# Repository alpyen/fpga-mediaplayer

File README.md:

# fpga-mediaplayer - learning FPGA development

Hi there, and welcome to my FPGA project to deep dive into FPGA development and everything around it.

Watch a demo of this project on YouTube by clicking on this picture!

## Navigation
1. [Introduction](#introduction)
2. [Project Goal](#project-goal)
3. [Top Level Overview](#top-level-overview)
4. [Documentation](#documentation)

## Introduction

This is a beginner project on hardware development with FPGAs and VHDL to create a system that can
play audio and video through an FPGA.

A FPGA development board -- here a <a href="https://digilent.com/reference/programmable-logic/basys-3/start">Digilent Basys3</a>
-- fetches audio and video data stored on the on-board flash memory chip,
decodes them and drives a <a href="https://digilent.com/reference/pmod/pmodi2s2/start">Digilent i2s2-PMOD</a>
for audio output and a custom designedLED matrix as the video display.

Originally the idea was to drive one of these standard Arduino LED shields (14x9 pixels) but that plan
was scrapped due to the very low resolution.

The key focus of this project was to accomplish this vision with certain -- partially arbitrary -- constraints
and to get the whole thing done while touching on many aspects of FPGA and electronics development.
It is by no means perfect, but it is done while hitting all the project's goals I set for myself.

## Project Goal

The main goal of this project was to get my hands dirty with all parts of FPGA development.
While the main focus is on the actual hardware description, a good amount of time was also spent
on developing the software and electronics side of things to get the full picture.

Besides getting this project actually done,
there were a lot of topics I wanted to cover (which includes, but is not limited to):
- Develop a full FPGA project with everything necessary
- Keep it flexible that it could run on different devices without too much additional effort
- Write HDL and verify with testbenches
- Write packages and make them accessible
- Make use of existing IP
- Prototyping
- Schematics, Layouting and Manufacturing a PCB
- Interface with other onboard components such as the flash memory
- Interface with prebuilt offboard components such as the Digilent I2S2 PMOD
- Interface with external offboard components such as the LED board
- Work within the limits of the given board such as the Digilent Basys3 (Artix7-35T)
  - 4MB Flash (only ~2MB with configuration)
  - Available IO
  - Clock Speed to maintain realtime
- Software development
  - Codec for audio and video
- Miscellaneous
  - Organization of project structure and repository for Git
  - Documentation of the whole project

Please note that these constraints emerged from the components and devices I have at disposal.
This project could be done with greater resolution and sound output but the goal is to bring it up
and learn everything along the way, that's the reason behind this approach.

## Top Level Overview

Here's a top level view of the system. It is build in a modular fashion encapsulating functionality
such that everything remains as local as possible so each module is easy to understand.
Dataflow is indicated by the directional arrows.

The Control Unit requests data from the memory driver which (here) accesses the onboard SPI flash.
It then alternately fills the Audio and Video FIFO which are read by the respective modules
on the other side. Those decode the data and fill up a FIFO for Audio and BRAMs for Video.
After the data is available the i2s Master and Board Driver will read the data at the correct time and
play them back by driving a Digilent i2s2 PMOD and a self designed LED multiplex display.

<picture>
    <source media="(prefers-color-scheme: dark)" srcset="docs/images/top-level-view-dark.png">
    
</picture>

## Documentation

A technical overview as well as project notes and decision making
can be found in the documentation.
Find the documentation overview [here](docs/README.md).

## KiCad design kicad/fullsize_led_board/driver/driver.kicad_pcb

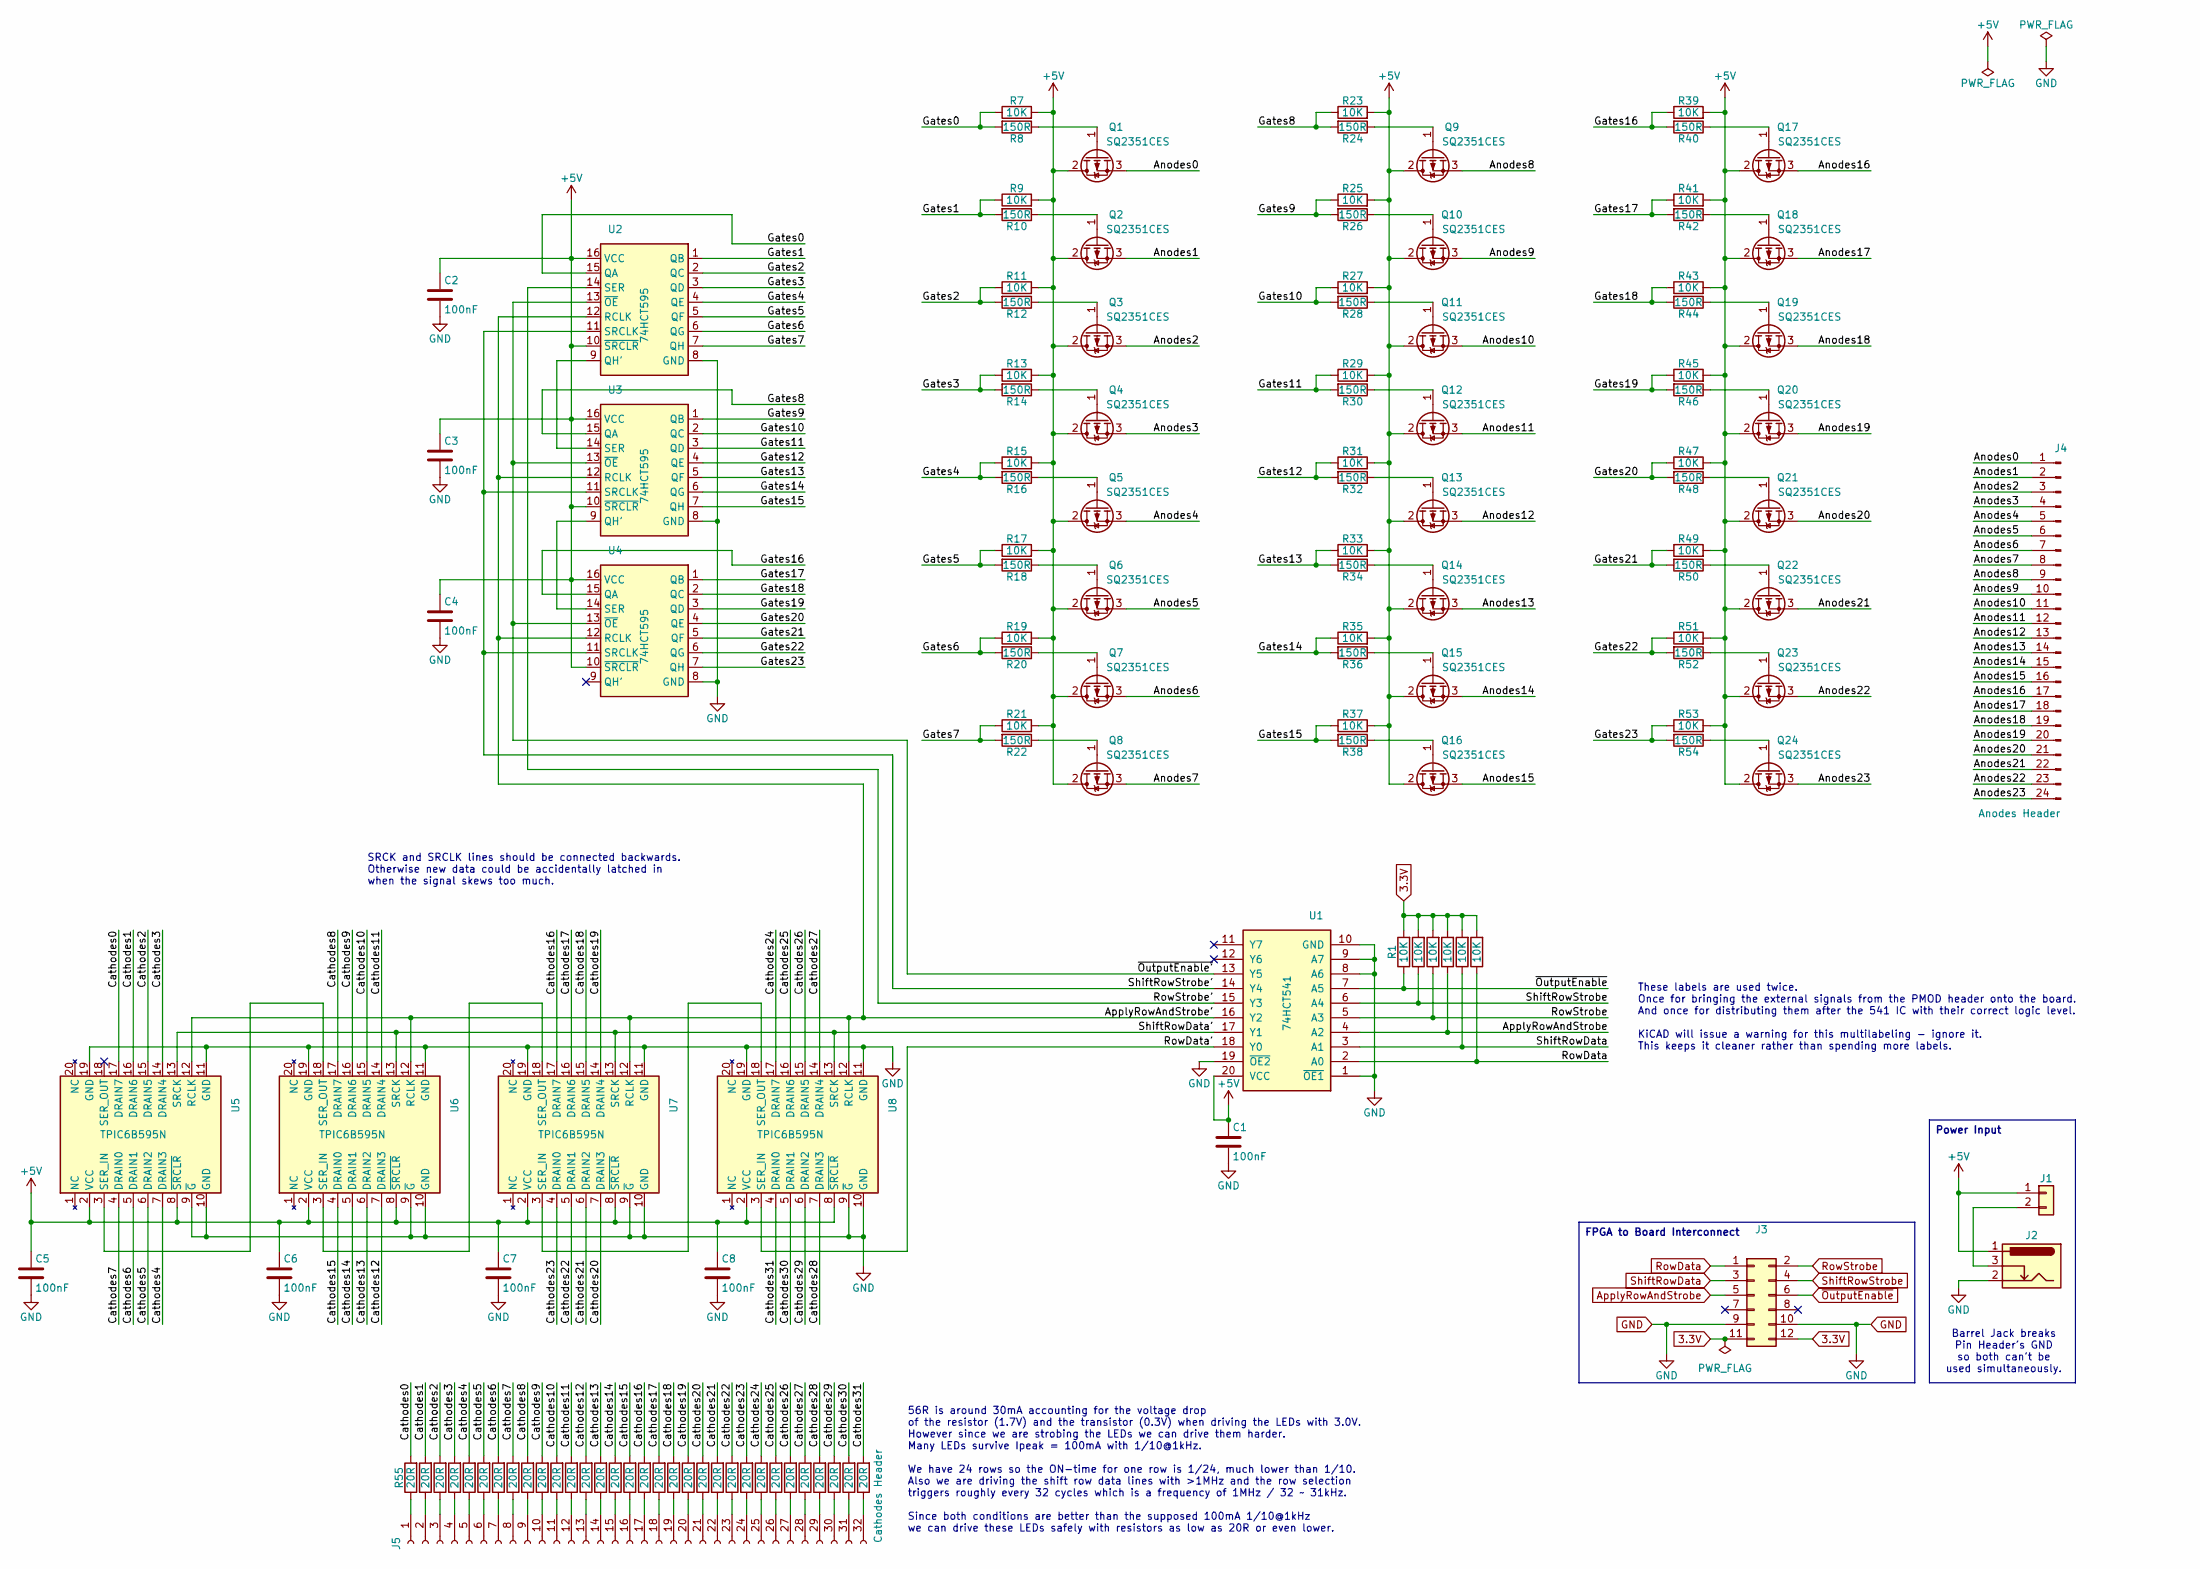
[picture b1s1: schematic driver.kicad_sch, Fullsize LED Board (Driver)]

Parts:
C1, C2, C3, C4, C5, C6, C7, C8: 100nF; C_Disc_D4.7mm_W2.5mm_P5.00mm
J1: PinHeader_1x02_P2.54mm_Horizontal
J2: BarrelJack_Horizontal
J3: PinHeader_2x06_P2.54mm_Horizontal
J4: Anodes Header; PinSocket_1x24_P2.54mm_Vertical
J5: Cathodes Header; PinSocket_1x32_P2.54mm_Vertical
Q1, Q2, Q3, Q4, Q5, Q6, Q7, Q8, Q9, Q10, Q11, Q12, Q13, Q14, Q15, Q16, Q17, Q18, Q19, Q20, Q21, Q22, Q23, Q24: SQ2351CES; SOT-23-3
R1, R2, R3, R4, R5, R6, R7, R9, R11, R13, R15, R17, R19, R21, R23, R25, R27, R29, R31, R33, R35, R37, R39, R41, R43, R45, R47, R49, R51, R53: 10K; R_Axial_DIN0207_L6.3mm_D2.5mm_P7.62mm_Horizontal
R8, R10, R12, R14, R16, R18, R20, R22, R24, R26, R28, R30, R32, R34, R36, R38, R40, R42, R44, R46, R48, R50, R52, R54: 150R; R_Axial_DIN0207_L6.3mm_D2.5mm_P7.62mm_Horizontal
R55, R56, R57, R58, R59, R60, R61, R62, R63, R64, R65, R66, R67, R68, R69, R70, R71, R72, R73, R74, R75, R76, R77, R78, R79, R80, R81, R82, R83, R84, R85, R86: 20R; R_Axial_DIN0207_L6.3mm_D2.5mm_P7.62mm_Horizontal
U1: 74HCT541; DIP-20_W7.62mm
U2, U3, U4: 74HCT595; SOIC-16_3.9x9.9mm_P1.27mm
U5, U6, U7, U8: TPIC6B595N; DIP-20_W7.62mm

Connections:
3.3V: J3.11, J3.12, R1.2, R2.2, R3.2, R4.2, R5.2, R6.2
+5V: C1.1, C2.1, C3.1, C4.1, C5.1, C6.1, C7.1, C8.1, J1.1, J2.1, Q1.2 (S), Q2.2 (S), Q3.2 (S), Q4.2 (S), Q5.2 (S), Q6.2 (S), Q7.2 (S), Q8.2 (S), Q9.2 (S), Q10.2 (S), Q11.2 (S), Q12.2 (S), Q13.2 (S), Q14.2 (S), Q15.2 (S), Q16.2 (S), Q17.2 (S), Q18.2 (S), Q19.2 (S), Q20.2 (S), Q21.2 (S), Q22.2 (S), Q23.2 (S), Q24.2 (S), R7.2, R9.2, R11.2, R13.2, R15.2, R17.2, R19.2, R21.2, R23.2, R25.2, R27.2, R29.2, R31.2, R33.2, R35.2, R37.2, R39.2, R41.2, R43.2, R45.2, R47.2, R49.2, R51.2, R53.2, U1.20 (VCC), U2.10 (~SRCLR), U2.16 (VCC), U3.10 (~SRCLR), U3.16 (VCC), U4.10 (~SRCLR), U4.16 (VCC), U5.2 (VCC), U5.8 (~SRCLR), U6.2 (VCC), U6.8 (~SRCLR), U7.2 (VCC), U7.8 (~SRCLR), U8.2 (VCC), U8.8 (~SRCLR)
/Anodes0: J4.1, Q1.3 (D)
/Anodes1: J4.2, Q2.3 (D)
/Anodes2: J4.3, Q3.3 (D)
/Anodes3: J4.4, Q4.3 (D)
/Anodes4: J4.5, Q5.3 (D)
/Anodes5: J4.6, Q6.3 (D)
/Anodes6: J4.7, Q7.3 (D)
/Anodes7: J4.8, Q8.3 (D)
/Anodes8: J4.9, Q9.3 (D)
/Anodes9: J4.10, Q10.3 (D)
/Anodes10: J4.11, Q11.3 (D)
/Anodes11: J4.12, Q12.3 (D)
/Anodes12: J4.13, Q13.3 (D)
/Anodes13: J4.14, Q14.3 (D)
/Anodes14: J4.15, Q15.3 (D)
/Anodes15: J4.16, Q16.3 (D)
/Anodes16: J4.17, Q17.3 (D)
/Anodes17: J4.18, Q18.3 (D)
/Anodes18: J4.19, Q19.3 (D)
/Anodes19: J4.20, Q20.3 (D)
/Anodes20: J4.21, Q21.3 (D)
/Anodes21: J4.22, Q22.3 (D)
/Anodes22: J4.23, Q23.3 (D)
/Anodes23: J4.24, Q24.3 (D)
/ApplyRowAndStrobe': U1.16 (Y2), U2.12 (RCLK), U3.12 (RCLK), U4.12 (RCLK), U5.12 (RCLK), U6.12 (RCLK), U7.12 (RCLK), U8.12 (RCLK)
/Cathodes0: R55.2, U5.17 (DRAIN7)
/Cathodes1: R56.2, U5.16 (DRAIN6)
/Cathodes2: R57.2, U5.15 (DRAIN5)
/Cathodes3: R58.2, U5.14 (DRAIN4)
/Cathodes4: R59.2, U5.7 (DRAIN3)
/Cathodes5: R60.2, U5.6 (DRAIN2)
/Cathodes6: R61.2, U5.5 (DRAIN1)
/Cathodes7: R62.2, U5.4 (DRAIN0)
/Cathodes8: R63.2, U6.17 (DRAIN7)
/Cathodes9: R64.2, U6.16 (DRAIN6)
/Cathodes10: R65.2, U6.15 (DRAIN5)
/Cathodes11: R66.2, U6.14 (DRAIN4)
/Cathodes12: R67.2, U6.7 (DRAIN3)
/Cathodes13: R68.2, U6.6 (DRAIN2)
/Cathodes14: R69.2, U6.5 (DRAIN1)
/Cathodes15: R70.2, U6.4 (DRAIN0)
/Cathodes16: R71.2, U7.17 (DRAIN7)
/Cathodes17: R72.2, U7.16 (DRAIN6)
/Cathodes18: R73.2, U7.15 (DRAIN5)
/Cathodes19: R74.2, U7.14 (DRAIN4)
/Cathodes20: R75.2, U7.7 (DRAIN3)
/Cathodes21: R76.2, U7.6 (DRAIN2)
/Cathodes22: R77.2, U7.5 (DRAIN1)
/Cathodes23: R78.2, U7.4 (DRAIN0)
/Cathodes24: R79.2, U8.17 (DRAIN7)
/Cathodes25: R80.2, U8.16 (DRAIN6)
/Cathodes26: R81.2, U8.15 (DRAIN5)
/Cathodes27: R82.2, U8.14 (DRAIN4)
/Cathodes28: R83.2, U8.7 (DRAIN3)
/Cathodes29: R84.2, U8.6 (DRAIN2)
/Cathodes30: R85.2, U8.5 (DRAIN1)
/Cathodes31: R86.2, U8.4 (DRAIN0)
/Gates0: R7.1, R8.2, U2.15 (QA)
/Gates1: R9.1, R10.2, U2.1 (QB)
/Gates2: R11.1, R12.2, U2.2 (QC)
/Gates3: R13.1, R14.2, U2.3 (QD)
/Gates4: R15.1, R16.2, U2.4 (QE)
/Gates5: R17.1, R18.2, U2.5 (QF)
/Gates6: R19.1, R20.2, U2.6 (QG)
/Gates7: R21.1, R22.2, U2.7 (QH)
/Gates8: R23.1, R24.2, U3.15 (QA)
/Gates9: R25.1, R26.2, U3.1 (QB)
/Gates10: R27.1, R28.2, U3.2 (QC)
/Gates11: R29.1, R30.2, U3.3 (QD)
/Gates12: R31.1, R32.2, U3.4 (QE)
/Gates13: R33.1, R34.2, U3.5 (QF)
/Gates14: R35.1, R36.2, U3.6 (QG)
/Gates15: R37.1, R38.2, U3.7 (QH)
/Gates16: R39.1, R40.2, U4.15 (QA)
/Gates17: R41.1, R42.2, U4.1 (QB)
/Gates18: R43.1, R44.2, U4.2 (QC)
/Gates19: R45.1, R46.2, U4.3 (QD)
/Gates20: R47.1, R48.2, U4.4 (QE)
/Gates21: R49.1, R50.2, U4.5 (QF)
/Gates22: R51.1, R52.2, U4.6 (QG)
/Gates23: R53.1, R54.2, U4.7 (QH)
/RowData': U1.18 (Y0), U8.3 (SER_IN)
/RowStrobe': U1.15 (Y3), U2.14 (SER)
/ShiftRowData': U1.17 (Y1), U5.13 (SRCK), U6.13 (SRCK), U7.13 (SRCK), U8.13 (SRCK)
/ShiftRowStrobe': U1.14 (Y4), U2.11 (SRCLK), U3.11 (SRCLK), U4.11 (SRCLK)
/~OutputEnable': U1.13 (Y5), U2.13 (~OE), U3.13 (~OE), U4.13 (~OE)
ApplyRowAndStrobe: J3.5, R4.1, U1.4 (A2)
GND: C1.2, C2.2, C3.2, C4.2, C5.2, C6.2, C7.2, C8.2, J2.2, J3.9, J3.10, U1.1 (~OE1), U1.8 (A6), U1.9 (A7), U1.10 (GND), U1.19 (~OE2), U2.8 (GND), U3.8 (GND), U4.8 (GND), U5.9 (~G), U5.10 (GND), U5.11 (GND), U5.19 (GND), U6.9 (~G), U6.10 (GND), U6.11 (GND), U6.19 (GND), U7.9 (~G), U7.10 (GND), U7.11 (GND), U7.19 (GND), U8.9 (~G), U8.10 (GND), U8.11 (GND), U8.19 (GND)
unnamed: J1.2, J2.3
unnamed: J5.1, R55.1
unnamed: J5.2, R56.1
unnamed: J5.3, R57.1
unnamed: J5.4, R58.1
unnamed: J5.5, R59.1
unnamed: J5.6, R60.1
unnamed: J5.7, R61.1
unnamed: J5.8, R62.1
unnamed: J5.9, R63.1
unnamed: J5.10, R64.1
unnamed: J5.11, R65.1
unnamed: J5.12, R66.1
unnamed: J5.13, R67.1
unnamed: J5.14, R68.1
unnamed: J5.15, R69.1
unnamed: J5.16, R70.1
unnamed: J5.17, R71.1
unnamed: J5.18, R72.1
unnamed: J5.19, R73.1
unnamed: J5.20, R74.1
unnamed: J5.21, R75.1
unnamed: J5.22, R76.1
unnamed: J5.23, R77.1
unnamed: J5.24, R78.1
unnamed: J5.25, R79.1
unnamed: J5.26, R80.1
unnamed: J5.27, R81.1
unnamed: J5.28, R82.1
unnamed: J5.29, R83.1
unnamed: J5.30, R84.1
unnamed: J5.31, R85.1
unnamed: J5.32, R86.1
unnamed: Q1.1 (G), R8.1
unnamed: Q2.1 (G), R10.1
unnamed: Q3.1 (G), R12.1
unnamed: Q4.1 (G), R14.1
unnamed: Q5.1 (G), R16.1
unnamed: Q6.1 (G), R18.1
unnamed: Q7.1 (G), R20.1
unnamed: Q8.1 (G), R22.1
unnamed: Q9.1 (G), R24.1
unnamed: Q10.1 (G), R26.1
unnamed: Q11.1 (G), R28.1
unnamed: Q12.1 (G), R30.1
unnamed: Q13.1 (G), R32.1
unnamed: Q14.1 (G), R34.1
unnamed: Q15.1 (G), R36.1
unnamed: Q16.1 (G), R38.1
unnamed: Q17.1 (G), R40.1
unnamed: Q18.1 (G), R42.1
unnamed: Q19.1 (G), R44.1
unnamed: Q20.1 (G), R46.1
unnamed: Q21.1 (G), R48.1
unnamed: Q22.1 (G), R50.1
unnamed: Q23.1 (G), R52.1
unnamed: Q24.1 (G), R54.1
unnamed: U2.9 (QH'), U3.14 (SER)
unnamed: U3.9 (QH'), U4.14 (SER)
unnamed: U5.3 (SER_IN), U6.18 (SER_OUT)
unnamed: U6.3 (SER_IN), U7.18 (SER_OUT)
unnamed: U7.3 (SER_IN), U8.18 (SER_OUT)
RowData: J3.1, R6.1, U1.2 (A0)
RowStrobe: J3.2, R3.1, U1.5 (A3)
ShiftRowData: J3.3, R5.1, U1.3 (A1)
ShiftRowStrobe: J3.4, R2.1, U1.6 (A4)
~OutputEnable: J3.6, R1.1, U1.7 (A5)

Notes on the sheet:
56R is around 30mA accounting for the voltage drop of the resistor (1.7V) and the transistor (0.3V) when driving the LEDs with 3.0V. However since we are strobing the LEDs we can drive them harder. Many LEDs survive Ipeak = 100mA with 1/10@1kHz. We have 24 rows so the ON-time for one row is 1/24, m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
Barrel Jack breaks Pin Header's GND so both can't be used simultaneously.
These labels are used twice. Once for bringing the external signals from the PMOD header onto the board. And once for distributing them after the 541 IC with their correct logic level. KiCAD will issue a warning for this multilabeling - ignore it. This keeps it cleaner rather than spending more lab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
SRCK and SRCLK lines should be connected backwards. Otherwise new data could be accidentally latched in when the signal skews too much.
Power Input
FPGA to Board Interconnect

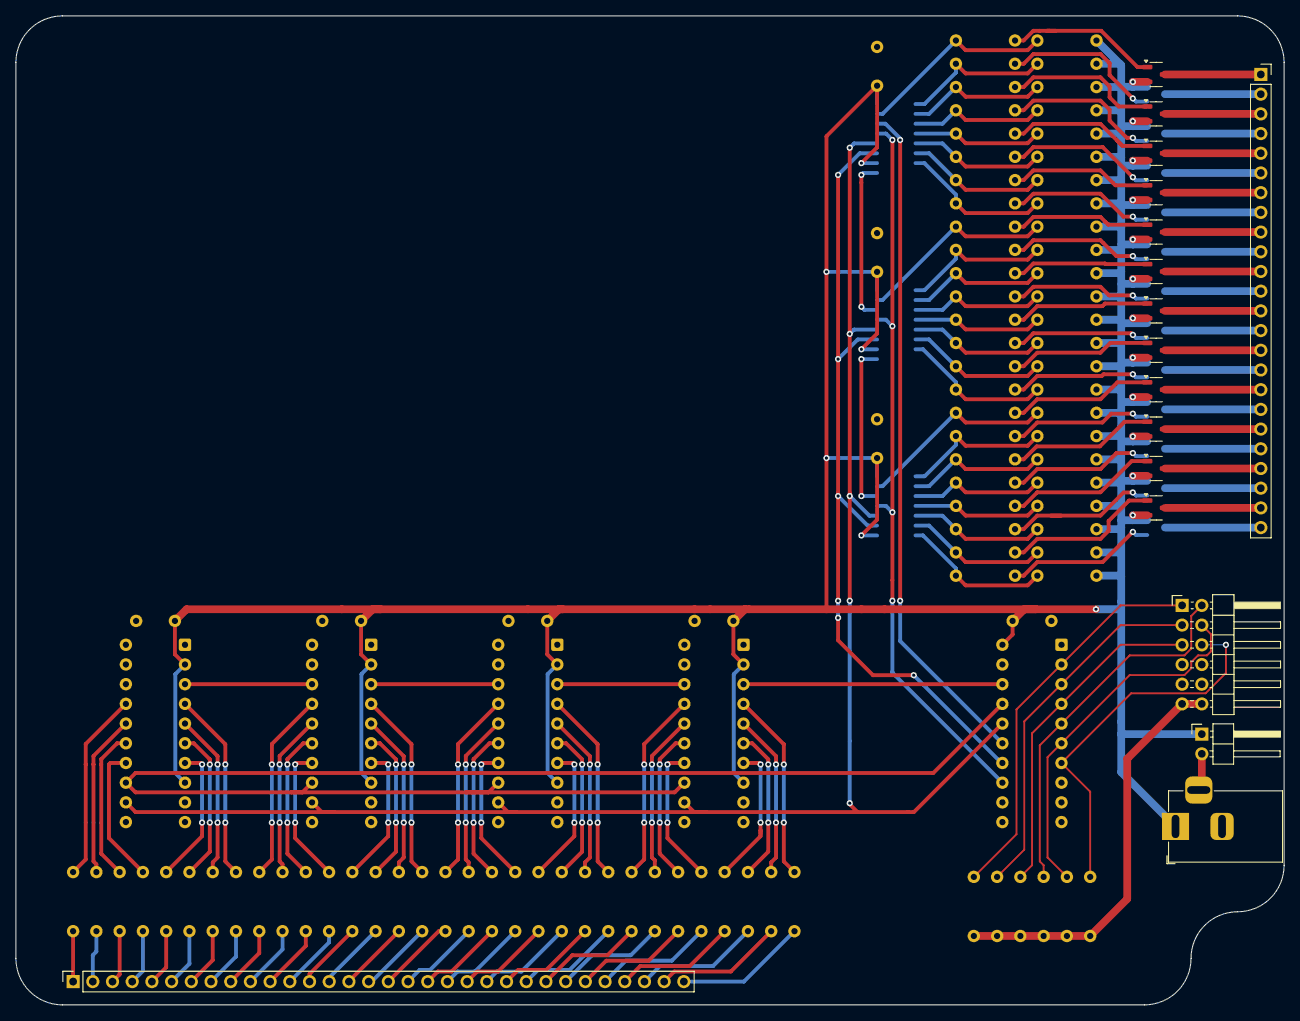
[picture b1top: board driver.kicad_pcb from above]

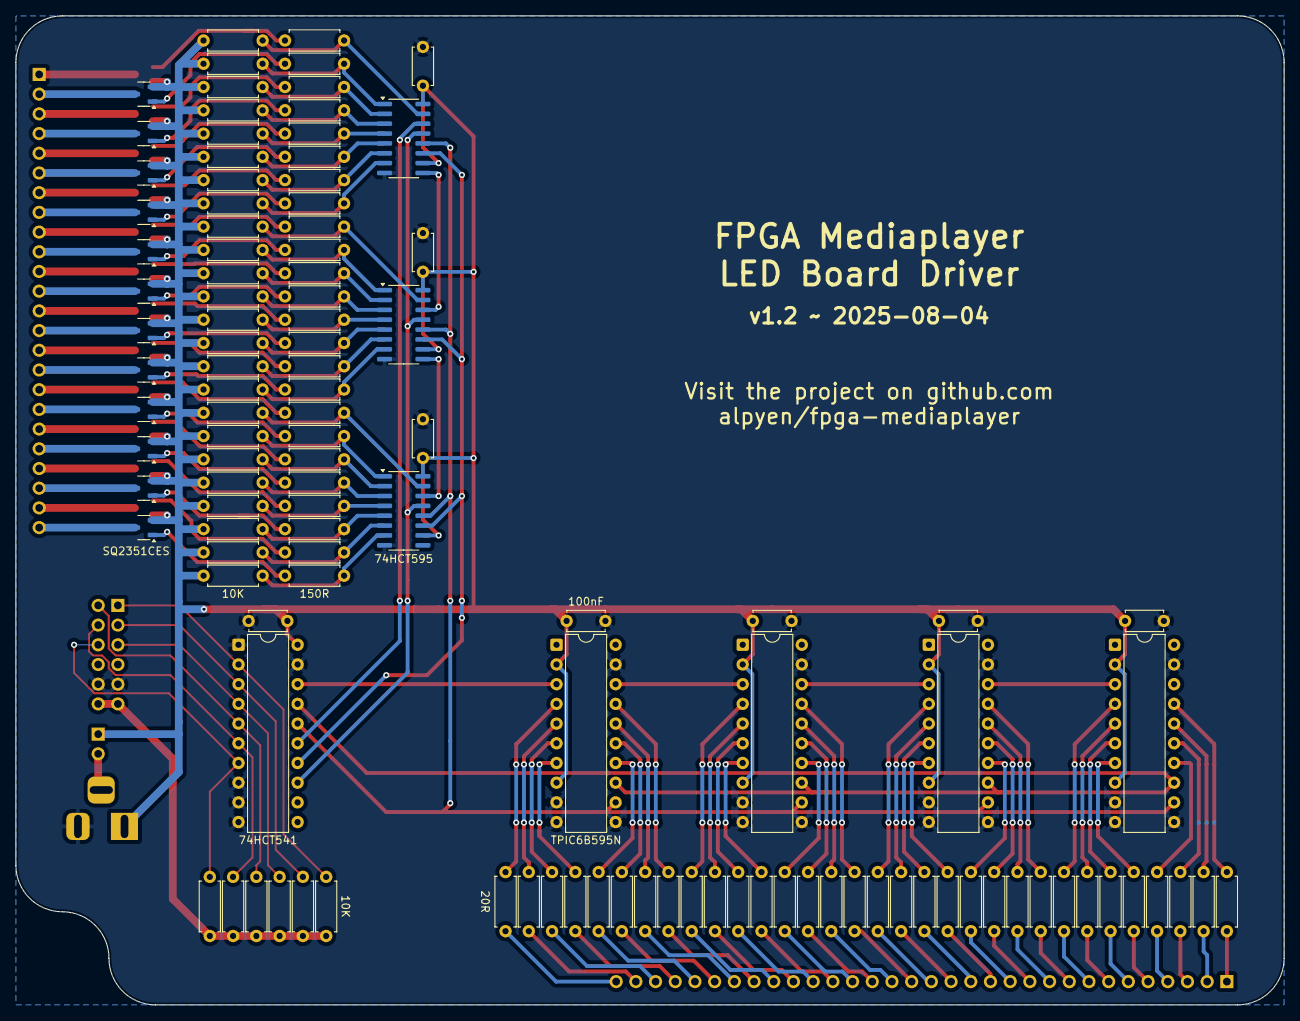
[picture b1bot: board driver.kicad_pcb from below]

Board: 2 copper layers, 163.5 x 127.5 mm, 131 parts (114 on the bottom side), 157 nets.

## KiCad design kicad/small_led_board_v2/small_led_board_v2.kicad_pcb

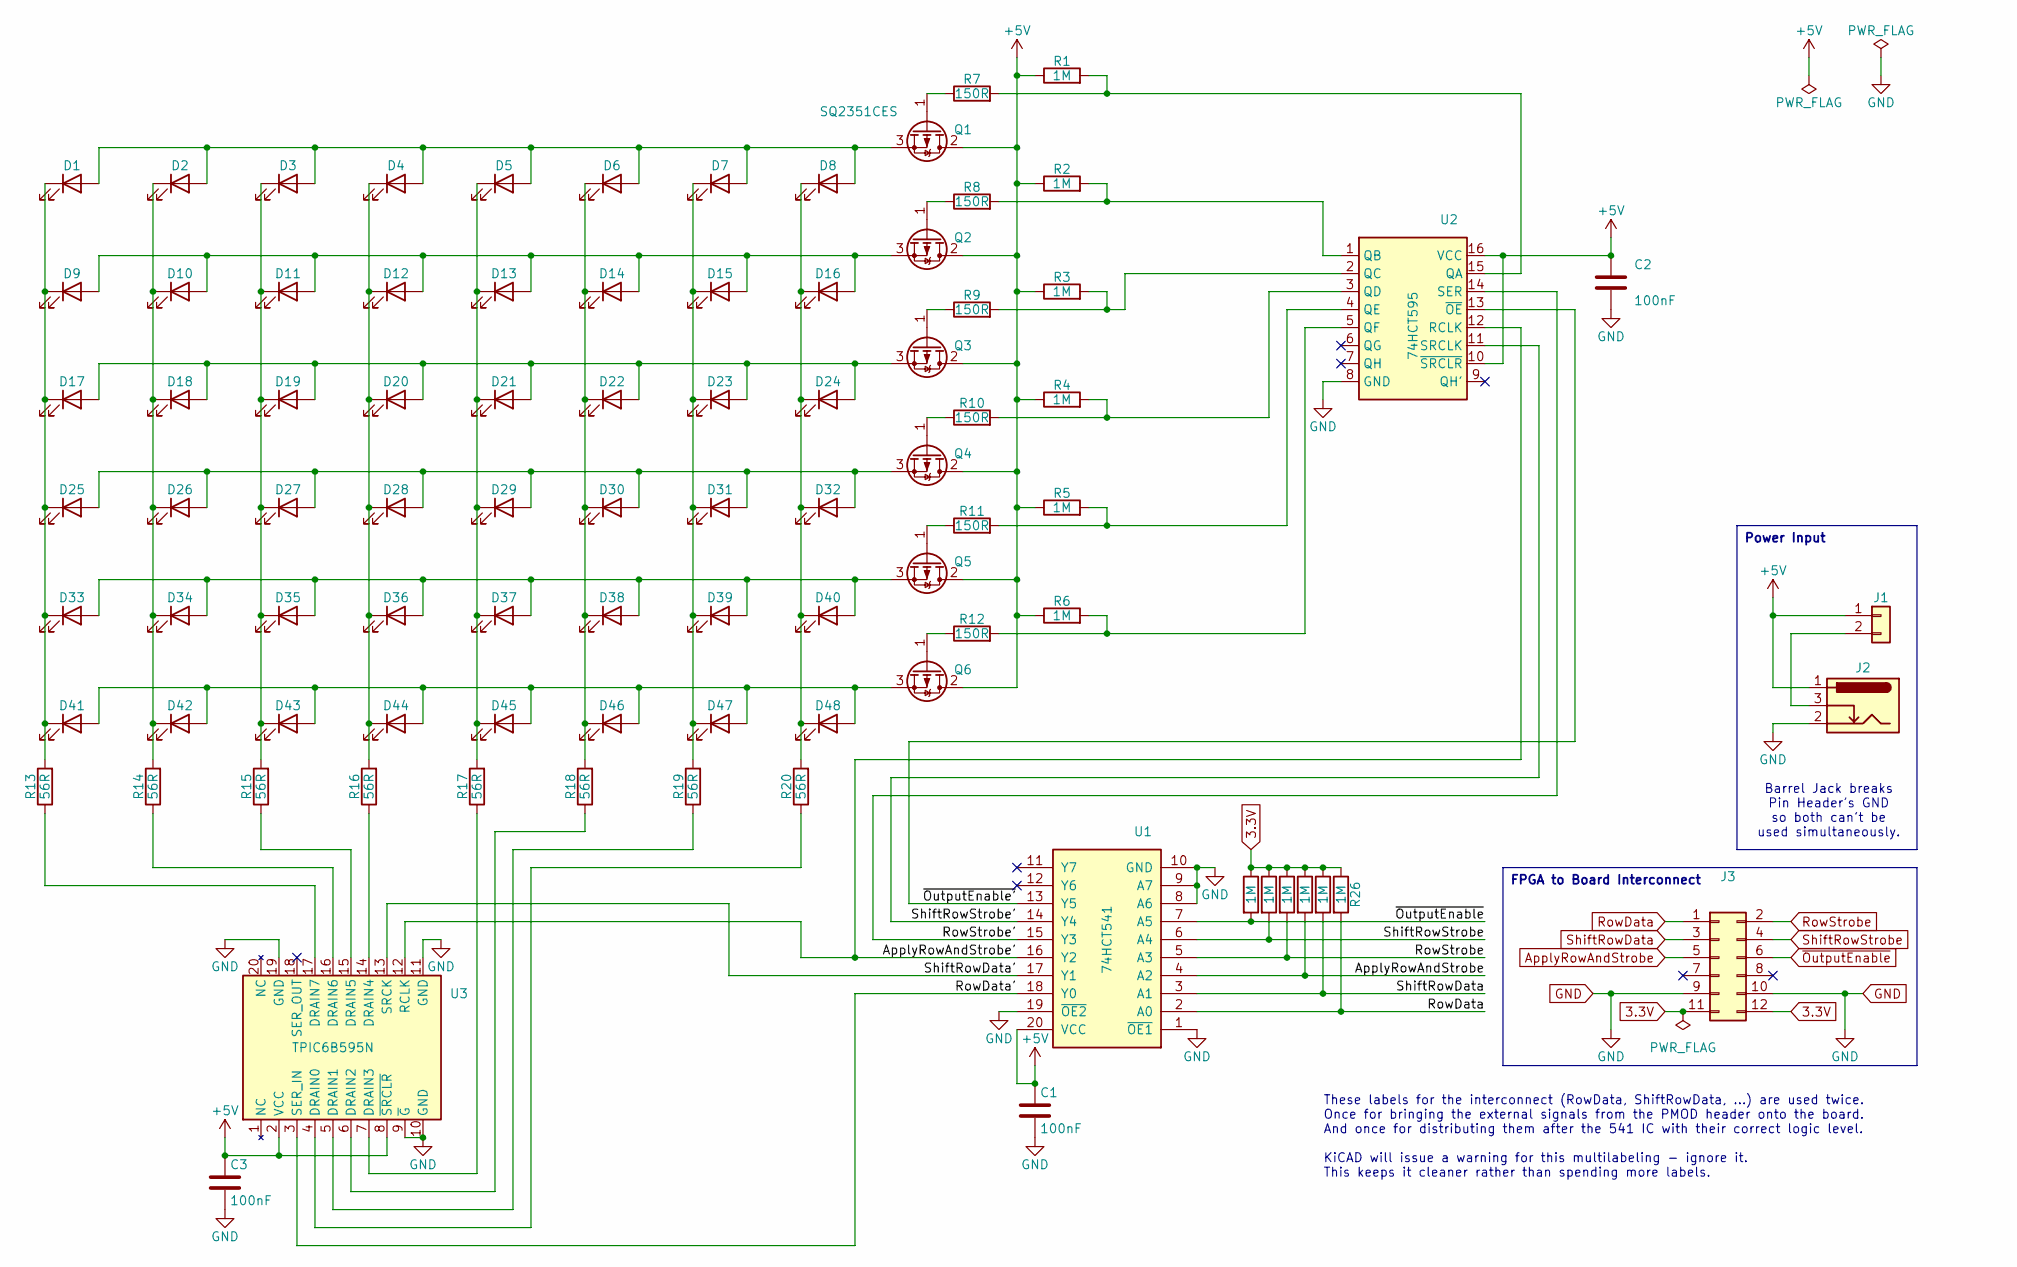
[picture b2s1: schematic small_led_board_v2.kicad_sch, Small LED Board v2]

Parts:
C1, C2, C3: 100nF; C_Disc_D4.7mm_W2.5mm_P5.00mm
D1, D2, D3, D4, D5, D6, D7, D8, D9, D10, D11, D12, D13, D14, D15, D16, D17, D18, D19, D20, D21, D22, D23, D24, D25, D26, D27, D28, D29, D30, D31, D32, D33, D34, D35, D36, D37, D38, D39, D40, D41, D42, D43, D44, D45, D46, D47, D48: LED; LED_D5.0mm
J1: PinHeader_1x02_P2.54mm_Horizontal
J2: BarrelJack_Horizontal
J3: PinHeader_2x06_P2.54mm_Horizontal
Q1, Q2, Q3, Q4, Q5, Q6: SQ2351CES; SOT-23-3
R1, R2, R3, R4, R5, R6, R21, R22, R23, R24, R25, R26: 1M; R_Axial_DIN0207_L6.3mm_D2.5mm_P7.62mm_Horizontal
R7, R8, R9, R10, R11, R12: 150R; R_Axial_DIN0207_L6.3mm_D2.5mm_P7.62mm_Horizontal
R13, R14, R15, R16, R17, R18, R19, R20: 56R; R_Axial_DIN0207_L6.3mm_D2.5mm_P7.62mm_Horizontal
U1: 74HCT541; DIP-20_W7.62mm
U2: 74HCT595; SOIC-16_3.9x9.9mm_P1.27mm
U3: TPIC6B595N; DIP-20_W7.62mm

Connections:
3.3V: J3.11, J3.12, R21.1, R22.1, R23.1, R24.1, R25.1, R26.1
+5V: C1.1, C2.1, C3.1, J1.1, J2.1, Q1.2 (S), Q2.2 (S), Q3.2 (S), Q4.2 (S), Q5.2 (S), Q6.2 (S), R1.1, R2.1, R3.1, R4.1, R5.1, R6.1, U1.20 (VCC), U2.10 (~SRCLR), U2.16 (VCC), U3.2 (VCC), U3.8 (~SRCLR)
/ApplyRowAndStrobe': U1.16 (Y2), U2.12 (RCLK), U3.12 (RCLK)
/RowData': U1.18 (Y0), U3.3 (SER_IN)
/RowStrobe': U1.15 (Y3), U2.14 (SER)
/ShiftRowData': U1.17 (Y1), U3.13 (SRCK)
/ShiftRowStrobe': U1.14 (Y4), U2.11 (SRCLK)
/~OutputEnable': U1.13 (Y5), U2.13 (~OE)
ApplyRowAndStrobe: J3.5, R24.2, U1.4 (A2)
GND: C1.2, C2.2, C3.2, J2.2, J3.9, J3.10, U1.1 (~OE1), U1.8 (A6), U1.9 (A7), U1.10 (GND), U1.19 (~OE2), U2.8 (GND), U3.9 (~G), U3.10 (GND), U3.11 (GND), U3.19 (GND)
unnamed: D1.2 (A), D2.2 (A), D3.2 (A), D4.2 (A), D5.2 (A), D6.2 (A), D7.2 (A), D8.2 (A), Q1.3 (D)
unnamed: D1.1 (K), D9.1 (K), D17.1 (K), D25.1 (K), D33.1 (K), D41.1 (K), R13.2
unnamed: D9.2 (A), D10.2 (A), D11.2 (A), D12.2 (A), D13.2 (A), D14.2 (A), D15.2 (A), D16.2 (A), Q2.3 (D)
unnamed: D2.1 (K), D10.1 (K), D18.1 (K), D26.1 (K), D34.1 (K), D42.1 (K), R14.2
unnamed: D3.1 (K), D11.1 (K), D19.1 (K), D27.1 (K), D35.1 (K), D43.1 (K), R15.2
unnamed: D4.1 (K), D12.1 (K), D20.1 (K), D28.1 (K), D36.1 (K), D44.1 (K), R16.2
unnamed: D5.1 (K), D13.1 (K), D21.1 (K), D29.1 (K), D37.1 (K), D45.1 (K), R17.2
unnamed: D6.1 (K), D14.1 (K), D22.1 (K), D30.1 (K), D38.1 (K), D46.1 (K), R18.2
unnamed: D7.1 (K), D15.1 (K), D23.1 (K), D31.1 (K), D39.1 (K), D47.1 (K), R19.2
unnamed: D8.1 (K), D16.1 (K), D24.1 (K), D32.1 (K), D40.1 (K), D48.1 (K), R20.2
unnamed: D17.2 (A), D18.2 (A), D19.2 (A), D20.2 (A), D21.2 (A), D22.2 (A), D23.2 (A), D24.2 (A), Q3.3 (D)
unnamed: D25.2 (A), D26.2 (A), D27.2 (A), D28.2 (A), D29.2 (A), D30.2 (A), D31.2 (A), D32.2 (A), Q4.3 (D)
unnamed: D33.2 (A), D34.2 (A), D35.2 (A), D36.2 (A), D37.2 (A), D38.2 (A), D39.2 (A), D40.2 (A), Q5.3 (D)
unnamed: D41.2 (A), D42.2 (A), D43.2 (A), D44.2 (A), D45.2 (A), D46.2 (A), D47.2 (A), D48.2 (A), Q6.3 (D)
unnamed: J1.2, J2.3
unnamed: Q1.1 (G), R7.1
unnamed: Q2.1 (G), R8.1
unnamed: Q3.1 (G), R9.1
unnamed: Q4.1 (G), R10.1
unnamed: Q5.1 (G), R11.1
unnamed: Q6.1 (G), R12.1
unnamed: R1.2, R7.2, U2.15 (QA)
unnamed: R2.2, R8.2, U2.1 (QB)
unnamed: R3.2, R9.2, U2.2 (QC)
unnamed: R4.2, R10.2, U2.3 (QD)
unnamed: R5.2, R11.2, U2.4 (QE)
unnamed: R6.2, R12.2, U2.5 (QF)
unnamed: R20.1, U3.4 (DRAIN0)
unnamed: R19.1, U3.5 (DRAIN1)
unnamed: R18.1, U3.6 (DRAIN2)
unnamed: R17.1, U3.7 (DRAIN3)
unnamed: R16.1, U3.14 (DRAIN4)
unnamed: R15.1, U3.15 (DRAIN5)
unnamed: R14.1, U3.16 (DRAIN6)
unnamed: R13.1, U3.17 (DRAIN7)
RowData: J3.1, R26.2, U1.2 (A0)
RowStrobe: J3.2, R23.2, U1.5 (A3)
ShiftRowData: J3.3, R25.2, U1.3 (A1)
ShiftRowStrobe: J3.4, R22.2, U1.6 (A4)
~OutputEnable: J3.6, R21.2, U1.7 (A5)

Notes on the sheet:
Barrel Jack breaks Pin Header's GND so both can't be used simultaneously.
These labels for the interconnect (RowData, ShiftRowData, ...) are used twice. Once for bringing the external signals from the PMOD header onto the board. And once for distributing them after the 541 IC with their correct logic level. KiCAD will issue a warning for this multilabeling - ignore it. T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
FPGA to Board Interconnect
Power Input

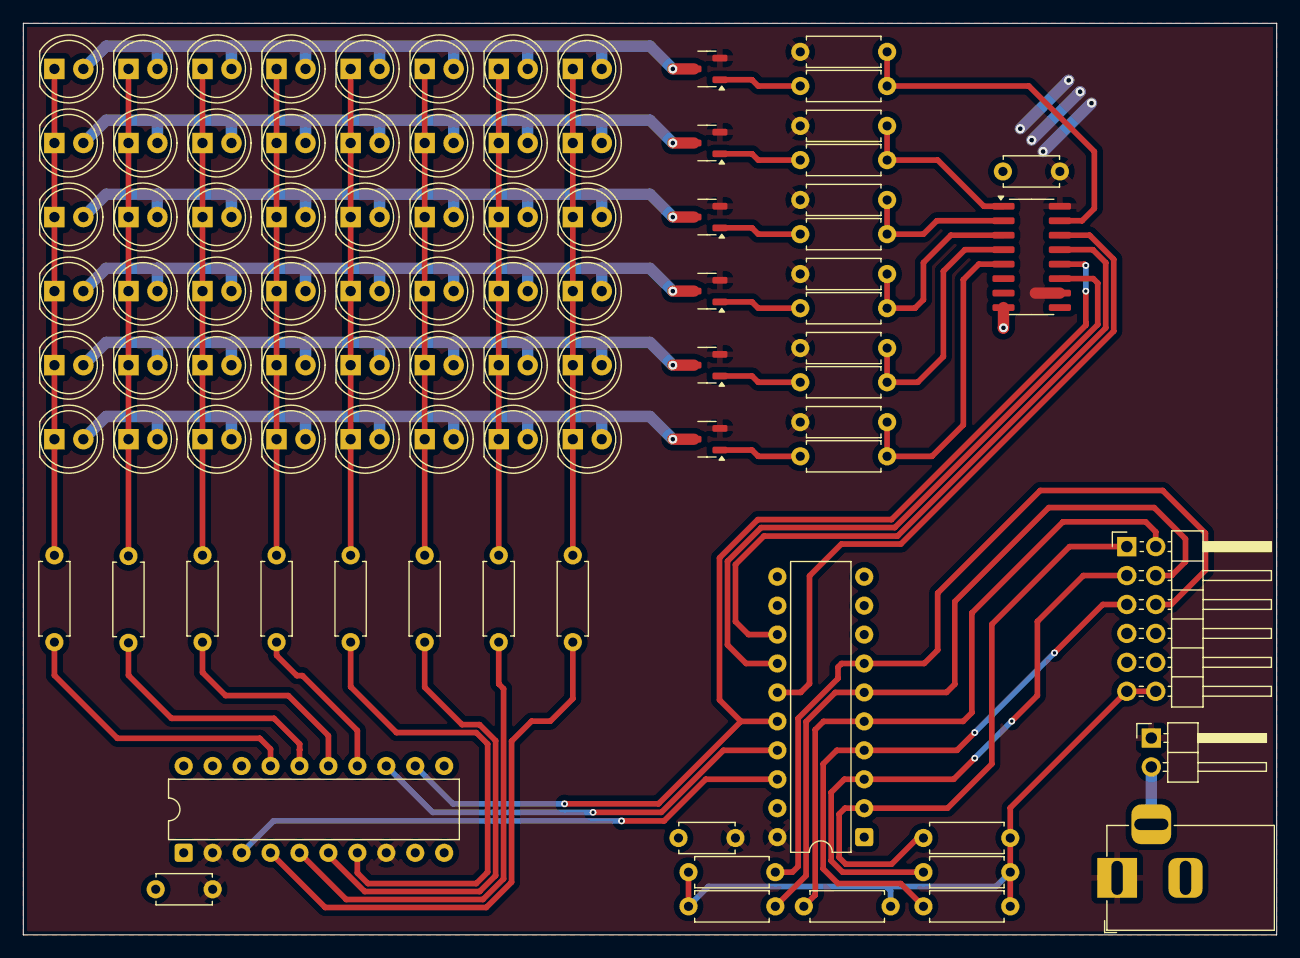
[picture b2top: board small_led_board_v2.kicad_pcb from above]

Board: 2 copper layers, 110.0 x 80.0 mm, 89 parts (0 on the bottom side), 50 nets.
